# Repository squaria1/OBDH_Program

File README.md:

Description
-----------
Cranfield University, 2025 NB-IoT satellite constellation Group Design Project (GDP),<br />
On Board Data Handling (OBDH) program, Telemetry, Tracking, and Command (TT&C) basecamp cFS application and payload program, Electrical Power System (EPS) board KiCad project.

EPS board KiCad project
-----------------------
The EPS board is made from the fusion of two existing open source projects from https://libre.solar/:
* The MPPT: https://github.com/LibreSolar/mppt-2420-hc
* The BMS: https://github.com/LibreSolar/bms-8s50-ic

See https://learn.libre.solar/ for the documentation and schematic explanation.<br />

Notable changes from the two source projects are:
* Complete board rerouting
* Add fuse to MPPT input
* Changed DC-DC 12V circuit
* BMS output into MPPT battery input
* Separate BMS and MPPT ground planes
* CAN connectors from RJ-45 to DB9
* Only one DB9 connector for both MPPT and BMS
* Battery charging connector from Molex to JST-XH 8 pos (for a 7S LiPo battery)

OBDH and payload programs requirements
------------
* cmake (>v3.10)
* g++
* git
* linux environnement (or VM, WSL)

Optional
--------
* Doxygen (for documentation generation)

Common installation
-------------------
Install required packages,
```
sudo apt install cmake build-essential doxygen git
```

Clone from the github repository,
```
cd ~
git clone https://github.com/squaria1/OBDH_Program.git
```

OBDH program installation
-------------------------
Build the OBDH program,
```
cd ~/OBDH_Program
mkdir build
cd build
cmake -S ../ -B .
make
```

Run the OBDH program,
```
cd ~/OBDH_Program/build
sudo ./OBDH_Program
```

(Optional) Generate OBDH program documentation with Doxygen,
```
cd ../../doc
doxygen Doxyfile
```

Then open html/index.html with a web browser.

Payload program installation
----------------------------
Build the Payload program,
```
cd ~/OBDH_Program/Payload_Program
mkdir build
cd build
cmake -S ../ -B .
make
```

Run the Payload program,
```
cd ~/OBDH_Program/Payload_Program/build
sudo ./Payload_Program
```

(Optional) Generate Payload program documentation with Doxygen,
```
cd ../doc
doxygen Doxyfile
```

Then open html/index.html with a web browser.

cFS basecamp TT&C application installation
------------------------------------------
Follow cFS basecamp installation instructions on https://github.com/cfs-tools/cfs-basecamp,<br />

Run the basecamp GUI with (where env/ and cfs-basecamp/ directories are located),
```
source env/bin/activate
cd cfs-basecamp/gnd-sys/app/
. ./setvars.sh
python3 basecamp.py
```

Create the hi_world tutorial application with the basecamp GUI,<br />
File-->Create user app-->Toggle Hello World-->Create App

Add the hi_world app to the cFS build configuration,<br />
File-->Add User App to Target-->Select "hi_world" in the dropdown-->Click on "Auto"-->Close window

Replace,
```
"APP_CMD_PIPE_DEPTH": 5
```
In "cfs-basecamp/cfe-eds-framework/basecamp_defs/cpu1_hi_world_ini.json"<br />
By,
```
"APP_CMD_PIPE_MAX": 7
```

Close basecamp,<br />
File-->Exit

Remove generated basecamp hi_world/ and copy hi_world/ from the git to the basecamp installation,
```
rm -R <<CHANGE TO YOUR BASECAMP ENV DIRECTORY>>/cfs-basecamp/usr/apps/hi_world
cp -r ~/OBDH_Program/basecamp_cFS_custom_app/hi_world <<CHANGE TO YOUR BASECAMP ENV DIRECTORY>>/cfs-basecamp/usr/apps/
```

Start basecamp again,
```
python3 basecamp.py
```

Build the application,<br />
Click on "Build New"

Start the application,<br />
Click on "Start"

Send telecommands (TCs) to the OBDH Program or payload Program (send to the OBDH and rerouted to the payload program through the CAN bus),<br />
"Send Cmd" dropdown-->Select HI_WORLD/Application/CMD-->Select "SetParam" in the dropdown-->Select main state to change (only one at a time)

Show recieved telemetry (TM),<br />
"View Tlm" dropdown-->Select HI_WORLD/Application/STATUS_TLM

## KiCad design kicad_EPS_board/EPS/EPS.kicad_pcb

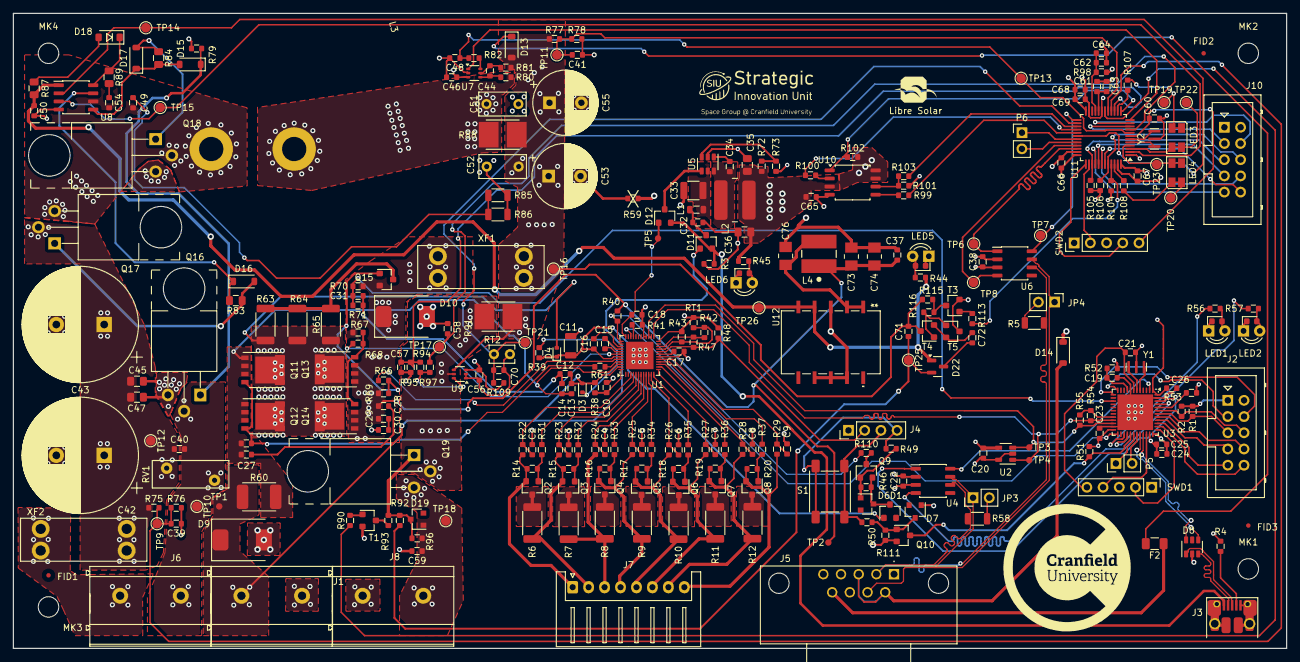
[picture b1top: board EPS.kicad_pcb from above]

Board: 4 copper layers, 199.5 x 99.5 mm, 305 parts (0 on the bottom side), 199 nets.

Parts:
C2, C3, C4, C5, C6, C7, C8, C9: 47n; C_0603_1608
C10: 470n; C_0603_1608
C11: 4.7u; C_1206_3216
C12, C14, C17, C32: 1u; C_0603_1608
C13: 10n; C_0603_1608
C15, C16, C31: 4.7n; C_0603_1608
C18, C19, C20, C21, C22, C23, C24, C26, C27, C28, C29, C30, C34: 100n; C_0603_1608
C25: 4.7u; C_0603_1608
C33: 4.7u; C_1210_3225
C35, C36: 10u; C_0805_2012
C37, C39, C40, C41, C57, C58, C59, C64, C72: 10nF; C_0603_1608
C38, C46, C54, C56, C60, C63, C65, C66, C67, C68, C70, C71: 100nF; C_0603_1608
C42, C43: 560µF; CP_Radial_D18.0mm_P7.50mm
C44, C48: 1nF; C_0603_1608
C45: 1µF; C_0805_2012
C47: 100nF; C_0805_2012
C49: 2.2nF; C_0603_1608
C50, C61, C62, C69: 2.2µF; C_0603_1608
C51, C52: 0.22µF; C_Rect_L7.2mm_W3.5mm_P5.00mm_FKS2_FKP2_MKS2_MKP2
C53, C55: 680µF; CP_Radial_D10.0mm_P5.00mm
C73, C74, C76: 4.7uF; CAPC370195_195N_KEM
D1, D11, D12: BAV70; SOT-23
D3, D4: PMEG6002; D_SOD-523
D6, D7, D19: 12V; D_SOT-23_ANK
D8: USBLC6-2SC6; SOT-23-6
D9, D10: SMCJ36A; D_SMC
D13, D14: NRVTS260ESFT1G; D_SOD-123
D15, D16, D17: SS14FL; D_SOD-123
D18: 1N4148; D_SOD-123
D22: BAS70-04; SOT-23
F2: 500mA; Fuse_1206_3216Metric
FID1, FID2, FID3: Fiducial; Fiducial_0.7mm
J1, J6, J8: MKDS 5/ 2-9,5; Phoenix_Contact_MKDS_5-2-9,5
J2, J10: UEXT; Box_Header_2x05x2.54mm_Straight
J3: USB_B_Micro; USB_Micro-B_10103594-0001LF
J4: Conn_01x04_Pin; PinHeader_1x04_P2.54mm_Vertical
J5: DE9_Receptacle; TE_2311765-1
J7: Conn_01x08_Pin; JST_XH_S8B-XH-A_1x08_P2.50mm_Horizontal
JP3, JP4: Jumper_NC_Small; PinHeader_1x02_P2.54mm_Vertical
L1: 4.7uH; L_0805_2012Metric
L2: 47uH; Bourns_SRN6045TA
L3: 53µH; Inductor_Toroid_D32.8mm_4mm2
L4: WE-PD2_5848
LED1, LED2, LED5, LED6: LED; LED_0603_D3.0mm
LED3, LED4: LED_Dual_PLCC4; LED_Avago_PLCC4_3.2x2.8mm_CW
LOGO1: LIBRE_SOLAR; LIBRESOLAR_LOGO
LOGO2: Cranfield University; cranfield_logo
LOGO3: Strategic Innovation Unit; strategic_innovation_unit
MK1, MK2, MK3, MK4: Mounting_Hole; MountingHole_3.2mm_M3
P5, P6: CONN_01X02; PinHeader_1x02_P2.54mm_Vertical
Q2, Q3, Q9: NDS0605; SOT-23
Q4, Q5, Q6, Q7, Q8, Q10, Q15: BSS138; SOT-23
Q11, Q12, Q13, Q14: BSC016N06NS; 5X6_MOSFET
Q16, Q17, Q18, Q19: IPA045N10N3G; TO-220-3_Horizontal_BottomHeatsink
R1, R2, R41, R54, R55, R76, R90, R97, R102, R105, R106: 2.2k; R_0603_1608
R3, R4, R14, R15, R16, R17, R18, R19, R20, R70: 330k; R_0603_1608
R5, R58: 120; R_1206_3216
R6, R7, R8, R9, R10, R11, R12: 33; R_2010_5025
R22, R23, R24, R25, R26, R27, R28, R29, R40, R44, R51, R56, R57, R82, R107, R108, R110, R116: 1k; R_0603_1608
R31, R32, R33, R34, R35, R36, R37, R43, R48, R49, R50, R93, R94, R109, R113: 10k; R_0603_1608
R38, R52, R61, R66, R68: 100; R_0603_1608
R39: 4R7; R_0603_1608
R42, R47, R71, R73: 22k; R_0603_1608
R45: 220; R_0603_1608
R46, R53, R62, R67, R69, R79, R96, R104, R111: 1M; R_0603_1608
R59: 0R; R_0603_1608
R60: 0.5m; R_Shunt_2512
R63, R64, R65: 330; R_2010_5025
R72: 50.5k; R_0603_1608
R75, R77, R92, R101, R115: 100k; R_0603_1608
R78: 5.6k; R_0603_1608
R80, R81: 10R; R_0603_1608
R83, R84, R87, R89: 3R3; R_0805_2012
R85, R86: 4R7; R_1206_3216
R88, R91: 2m; R_Bourns_CRE2512
R95: 8.2k; C_0603_1608
R98, R99, R100, R103: 47R; R_0603_1608
RT1: 10k; R_0603_1608
RT2: 10k; C_Disc_D3.8mm_W2.6mm_P2.50mm
RV1: 82V; RV_Disc_D12mm_W4.3mm_P7.5mm
S1: SW_PUSH; SW_SPST_6mm
SWD1: ST_Nucleo_SWD_5p; PinHeader_1x05_P2.54mm_Vertical
SWD2: ST_Nucleo_SWD; PinHeader_1x05_P2.54mm_Vertical
T1, T3, T4: BC846B; SOT-23
T5: BC856B; SOT-23
TP1: Bat+; TestPoint_1mm_pad
TP2: Ext+; TestPoint_1mm_pad
TP3: SDA; TestPoint_1mm_pad
TP4: SCL; TestPoint_1mm_pad
TP5: Regout; TestPoint_1mm_pad
TP6, TP7, TP8, TP9, TP10, TP11, TP12, TP13, TP14, TP15, TP16, TP17, TP18, TP19, TP20, TP21, TP22, TP23, TP25, TP26: 1.5mm; TestPoint_Pad_D1.5mm
U1: ISL94202; QFN-48-1EP_6x6mm_P0.4mm_EP4.3x4.3mm
U2: 24AA32; SOT-23-5
U3: STM32L452CCU6; QFN-48-1EP_7x7mm_P0.5mm_EP5.6x5.6mm
U4, U6: TCAN334; SOIC-8_3.9x4.9mm_Pitch1.27mm
U5: TPS560430X; SOT-23-6
U7, U9: INA186; SOT-363_SC-70-6
U8: LM5107; SOIC-8_3.9x4.9mm_Pitch1.27mm
U10: W25Q80DVS; SOIC-8_5.23x5.23mm_P1.27mm
U11: STM32G431CBTx; LQFP-48_7x7mm_P0.5mm
U12: TSR 0.5-24120SM; TSR 0.5SM_TRP
XF1, XF2: Fuse_Holder; Keystone-Fuse-3557-2
Y1, Y2: 8MHz; Resonator_Murata_CSTNE

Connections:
+3V3: C20.1, C22.1, C23.1, C24.1, C25.1, C26.1, C35.1, C36.1, C38.1, C46.1, C56.1, C65.1, C66.1, C67.1, C68.1, C69.1, J2.1 (3V3), J10.1 (3V3), L2.2, R1.2, R2.2, R45.2, R51.2, R52.2, R72.1, R98.2, R102.2, R105.2, R106.2, R109.1, SWD1.1 (VCC), SWD2.1 (VCC), U2.4 (VCC), U3.1 (VBAT), U3.24 (VDD), U3.36 (VDDUSB), U3.48 (VDD), U4.3 (VCC), U6.3 (VCC), U7.3 (V+), U9.3 (V+), U10.3 (IO2), U10.7 (IO3), U10.8 (VCC), U11.1 (VBAT), U11.24 (VDD), U11.36 (VDD), U11.48 (VDD)
+5V_BMS: D11.2 (A), D12.2 (A), J3.1 (VBUS), R3.1
+12V: C50.1, D22.1, R44.2, R87.2, TP26.1, U8.1 (VDD), U12.4 (+VOUT), U12.5 (+VOUT)
/8S BMS/BAT+: C12.1, C13.1, D3.2 (A), D9.1 (K), D11.1 (A), J1.1, R38.1, R60.2, TP1.1, U1.47 (CSI1)
/8S BMS/CAN_BMS_N: J5.2, R5.2, R58.2, U4.6 (CANL), U6.6 (CANL)
/8S BMS/CAN_BMS_P: J5.7, JP3.1, JP4.1, U4.7 (CANH), U6.7 (CANH)
/8S BMS/EXT+: C28.2, C29.1, C37.1, C73.1, C74.1, D10.1 (K), L4.1, Q13.S, Q14.S, Q15.2 (S), R40.1, R67.1, R69.1, R70.1, TP2.1, XF1.2
/8S BMS/ISL94202/ALERT: U1.34 (~SD), U3.25 (PB12)
/8S BMS/ISL94202/BTN_1: J4.4, R49.1, S1.2
/8S BMS/ISL94202/BTN_2: J4.3, R50.2, S1.1
/8S BMS/ISL94202/BTN_SIGNAL: Q10.3 (D), R51.1, U3.29 (PA8)
/8S BMS/ISL94202/CB1: R37.1, U1.16 (CB1)
/8S BMS/ISL94202/CB2: R36.1, U1.14 (CB2)
/8S BMS/ISL94202/CB3: R35.1, U1.12 (CB3)
/8S BMS/ISL94202/CB4: R34.1, U1.10 (CB4)
/8S BMS/ISL94202/CB5: R33.1, U1.8 (CB5)
/8S BMS/ISL94202/CB6: R32.1, U1.6 (CB6)
/8S BMS/ISL94202/CB7: R31.1, U1.4 (CB7)
/8S BMS/ISL94202/CELL1+: J7.7, Q7.2 (S), R12.2, R19.1, R28.2
/8S BMS/ISL94202/CELL1-: J7.8, Q8.2 (S), R20.1, R29.2
/8S BMS/ISL94202/CELL2+: J7.6, Q6.2 (S), R11.2, R18.1, R27.2
/8S BMS/ISL94202/CELL3+: J7.5, Q5.2 (S), R10.2, R17.1, R26.2
/8S BMS/ISL94202/CELL4+: J7.4, Q4.2 (S), R9.2, R16.1, R25.2
/8S BMS/ISL94202/CELL5+: J7.3, R7.1, R8.2, R24.2
/8S BMS/ISL94202/CELL6+: J7.2, Q3.2 (S), R6.1, R15.2, R23.2
/8S BMS/ISL94202/CELL7+: J7.1, Q2.2 (S), R14.2, R22.2
/8S BMS/ISL94202/CFET: R61.2, U1.45 (CFET)
/8S BMS/ISL94202/CHG+: D4.2 (A), Q11.D, Q12.D, Q13.D, Q14.D, R63.2, R64.2, R65.2
/8S BMS/ISL94202/CHMON: R40.2, R110.1, U1.37 (CHMON), U1.38 (LDMON)
/8S BMS/ISL94202/CSI2: C13.2, C14.1, C27.1, Q11.S, Q12.S, R60.1, R62.2, U1.46 (CSI2)
/8S BMS/ISL94202/DFET: R68.1, U1.42 (DFET)
/8S BMS/ISL94202/NTC_BAT: J4.2, R47.1, R48.2, U1.20 (XT1)
/8S BMS/ISL94202/PCFET: R66.2, U1.44 (PCFET)
/8S BMS/ISL94202/RGO: C18.1, D12.1 (A), TP5.1, U1.36 (RGO)
/8S BMS/ISL94202/SCL: R54.1, TP4.1, U1.25 (SCL), U2.1 (SCL), U3.21 (PB10)
/8S BMS/ISL94202/SDA: R55.1, TP3.1, U1.26 (SDAI), U1.27 (SDAO), U2.3 (SDA), U3.22 (PB11)
/8S BMS/ISL94202/TEMPO: R42.2, R47.2, U1.22 (TEMPO)
/8S BMS/ISL94202/VC0: C9.1, R29.1, U1.17 (VC0)
/8S BMS/ISL94202/VC1: C8.1, R28.1, U1.15 (VC1)
/8S BMS/ISL94202/VC2: C7.1, R27.1, U1.13 (VC2)
/8S BMS/ISL94202/VC3: C6.1, R26.1, U1.11 (VC3)
/8S BMS/ISL94202/VC4: C5.1, R25.1, U1.9 (VC4)
/8S BMS/ISL94202/VC5: C4.1, R24.1, U1.7 (VC5)
/8S BMS/ISL94202/VC6: C3.1, R23.1, U1.5 (VC6)
/8S BMS/ISL94202/VC7: C2.1, R22.1, U1.3 (VC7)
/8S BMS/ISL94202/VDD: C11.1, C16.1, D1.1 (A), D4.1 (K), R39.1, U1.43 (VDD)
/8S BMS/ISL94202/XT2: R42.1, R43.2, RT1.1, U1.21 (XT2)
/8S BMS/MCU/BOOT0: R53.2, U3.44 (PH3)
/8S BMS/MCU/CAN_RX: U3.45 (PB8), U4.4 (RXD)
/8S BMS/MCU/CAN_STB: U3.2 (PC13), U4.8 (STB)
/8S BMS/MCU/CAN_TX: U3.46 (PB9), U4.1 (TXD)
/8S BMS/MCU/I2C1_SCL: J2.5 (SCL), R1.1, U3.42 (PB6)
/8S BMS/MCU/I2C1_SDA: J2.6 (SDA), R2.1, U3.43 (PB7)
/8S BMS/MCU/I2C2_PULLUP: R54.2, R55.2, U3.20 (PB2)
/8S BMS/MCU/LED1: R56.2, U3.27 (PB14)
/8S BMS/MCU/LED2: R57.2, U3.28 (PB15)
/8S BMS/MCU/SPI1_MISO: J2.7 (MISO), U3.40 (PB4)
/8S BMS/MCU/SPI1_MOSI: J2.8 (MOSI), U3.41 (PB5)
/8S BMS/MCU/SPI1_SCK: J2.9 (SCK), U3.39 (PB3)
/8S BMS/MCU/SSEL: J2.10 (SSEL), U3.38 (PA15)
/8S BMS/MCU/SWCLK: SWD1.2 (SWCLK), U3.37 (PA14)
/8S BMS/MCU/SWDIO: SWD1.4 (SWDIO), U3.34 (PA13)
/8S BMS/MCU/USART1_RX: P5.2, U3.31 (PA10)
/8S BMS/MCU/USART1_TX: P5.1, U3.30 (PA9)
/8S BMS/MCU/USART2_RX: J2.4 (RXD), U3.13 (PA3)
/8S BMS/MCU/USART2_TX: J2.3 (TXD), U3.12 (PA2)
/8S BMS/MCU/USB_D+: D8.1 (IO1), J3.3 (D+)
/8S BMS/MCU/USB_D-: D8.3 (IO2), J3.2 (D-)
/8S BMS/MCU/USB_DN: D8.4 (IO2), U3.32 (PA11)
/8S BMS/MCU/USB_DP: D8.6 (IO1), U3.33 (PA12)
/8S BMS/MCU/~RESET: C21.1, SWD1.5 (NRST), U3.7 (NRST)
/8S BMS/Power Supply/EN: D12.3 (K), U5.4 (EN)
/8S BMS/Power Supply/FB: R72.2, R73.1, U5.3 (FB)
/8S BMS/Power Supply/SW: C34.2, L2.1, U5.6 (SW)
/8S BMS/Power Supply/VIN: C33.1, L1.2, U5.5 (Vin)
/8S BMS/V_EXT: C31.1, R70.2, R71.1, U3.15 (PA5)
/CAN_GND: D14.2 (A), J5.3, J5.6
/CAN_PWR: F2.1, J5.9
/MPPT/CAN/CAN_RX: TP8.1, U6.4 (RXD), U11.33 (PA11)
/MPPT/CAN/CAN_STB: TP7.1, U6.8 (STB), U11.25 (PB11)
/MPPT/CAN/CAN_TX: TP6.1, U6.1 (TXD), U11.34 (PA12)
/MPPT/DCDC/HS_DRV: D16.1 (K), R83.2, U8.7 (HO)
/MPPT/DCDC/I_DCDC: C48.1, R82.2, TP13.1, U11.8 (PA0)
/MPPT/DCDC/I_DCDC_REF: U7.1 (REF), U11.12 (PA4)
/MPPT/DCDC/LS_DRV: D15.2 (A), D17.1 (K), R84.2, U8.5 (LO)
/MPPT/DCDC/PWM_HS: TP14.1, U8.2 (HI), U11.30 (PA8)
/MPPT/DCDC/PWM_LS: TP15.1, U8.3 (LI), U11.2 (PC13)
/MPPT/DCDC/SHUNT_DCDC_P: C51.1, L3.2, R80.1, R88.2
/MPPT/DCDC/SW_NODE: C49.1, C54.2, L3.1, Q17.3 (S), Q18.2 (D), U8.6 (HS)
/MPPT/DCDC/V_DCDC_H: C39.1, R75.2, R76.1, TP9.1, U11.16 (PB0)
/MPPT/DCDC/V_DCDC_L: C41.1, R77.2, R78.1, TP11.1, U11.17 (PB1)
/MPPT/DCDC_HV+: C40.1, C42.1, C43.1, C45.1, C47.1, Q17.2 (D), R75.1, RV1.1, TP12.1, XF2.2
/MPPT/DCDC_HV-: C40.2, J6.2, Q16.2 (D), RV1.2, TP10.1
/MPPT/LOAD+: C59.1, D19.2 (A), J8.2, Q19.3 (S), R96.2, TP18.1
/MPPT/Load switch/CP_OUT: C71.1, D22.2, R92.1, TP25.1
/MPPT/Load switch/I_LOAD: C58.1, R97.2, TP17.1, U11.9 (PA1)
/MPPT/Load switch/I_LOAD_COMP: C57.1, R94.1, R95.2, U11.15 (PA7)
/MPPT/Load switch/LOAD_DIS: R90.1, U11.18 (PB2)
/MPPT/Load switch/SHUNT_LOAD_N: Q19.2 (D), R91.1, U9.5 (-)
/MPPT/MCU1/ADC1_IN11: C70.1, R109.2, RT2.1, TP21.1, U11.26 (PB12)
/MPPT/MCU1/GPIOC_14: LED3.2 (K1), LED3.3 (A2), TP22.1, U11.3 (PC14-OSC32_IN)
/MPPT/MCU1/GPIOC_15: LED4.2 (K1), LED4.3 (A2), TP23.1, U11.4 (PC15-OSC32_OUT)
/MPPT/MCU1/I2C1_SCL: J10.5 (SCL), R105.1, U11.39 (PA15)
/MPPT/MCU1/I2C1_SDA: J10.6 (SDA), R106.1, U11.44 (PB7)
/MPPT/MCU1/OSC_IN: U11.5 (PF0-OSC_IN), Y2.3
/MPPT/MCU1/OSC_OUT: U11.6 (PF1-OSC_OUT), Y2.1
/MPPT/MCU1/SPI1_MISO: J10.7 (MISO), U11.41 (PB4)
/MPPT/MCU1/SPI1_MOSI: J10.8 (MOSI), U11.42 (PB5)
/MPPT/MCU1/SPI1_SCK: J10.9 (SCK), U11.40 (PB3)
/MPPT/MCU1/SPI1_SSEL: J10.10 (SSEL), U11.43 (PB6)
/MPPT/MCU1/SPI2_CS: R102.1, U10.1 (~CS), U11.13 (PA5)
/MPPT/MCU1/SPI2_MISO: R100.1, U11.28 (PB14)
/MPPT/MCU1/SPI2_MOSI: R99.1, U11.29 (PB15)
/MPPT/MCU1/SPI2_SCK: R103.2, U11.27 (PB13)
/MPPT/MCU1/SWCLK: SWD2.2 (SWCLK), U11.38 (PA14)
/MPPT/MCU1/SWDIO: SWD2.4 (SWDIO), U11.37 (PA13)
/MPPT/MCU1/TIM8_CH2: R104.2, R113.2, U11.45 (PB8-BOOT0)
/MPPT/MCU1/TIM16_CH1: R107.2, U11.14 (PA6)
/MPPT/MCU1/TIM17_CH1: R108.2, U11.46 (PB9)
/MPPT/MCU1/USART1_RX: P6.2, U11.32 (PA10)
/MPPT/MCU1/USART1_TX: P6.1, U11.31 (PA9)
/MPPT/MCU1/USART2_RX: J10.4 (RXD), U11.11 (PA3)
/MPPT/MCU1/USART2_TX: J10.3 (TXD), U11.10 (PA2)
/MPPT/MCU1/~RESET: C60.1, SWD2.5 (NRST), U11.7 (NRST)
/MPPT/Power supply/CP_SW: C72.2, T4.2 (E), T5.2 (E)
/MPPT/Solar+: J6.1, XF2.1
GND: C30.2, C37.2, C38.2, C39.2, C41.2, C42.2, C43.2, C45.2, C46.2, C47.2, C48.2, C50.2, C51.2, C52.1, C53.2, C55.2, C56.2, C57.2, C58.2, C59.2, C60.2, C61.2, C62.2, C63.2, C64.2, C65.2, C66.2, C67.2, C68.2, C69.2, C70.2, C73.2, C74.2, C76.2, D9.2 (A), D10.2 (A), D14.1 (K), J1.2, J8.1, J10.2 (GND), LED5.1 (K), Q16.3 (S), Q18.3 (S), R59.1, R76.2, R78.2, R79.2, R85.1, R86.1, R95.1, R101.1, R104.1, RT2.2, SWD2.3 (GND), T1.2 (E), T3.2 (E), T5.3 (C), U6.2 (GND), U7.2 (GND), U8.4 (VSS), U9.1 (REF), U9.2 (GND), U10.4 (GND), U11.19 (VSSA), U11.23 (VSS), U11.35 (VSS), U11.47 (VSS), U12.3 (GGND), U12.7 (GND), U12.8 (GND), U12.9 (GND), Y2.2
GND_BMS: C2.2, C3.2, C4.2, C5.2, C6.2, C7.2, C8.2, C9.2, C10.2, C11.2, C12.2, C14.2, C17.2, C18.2, C19.2, C20.2, C21.2, C22.2, C23.2, C24.2, C25.2, C26.2, C31.2, C32.2, C33.2, C35.2, C36.2, D7.2 (A), D8.2 (GND), J2.2 (GND), J3.5 (GND), J3.6 (Shield), J4.1, LED1.1 (K), LED2.1 (K), LED6.1 (K), Q10.2 (S), R3.2, R4.2, R41.2, R43.1, R48.1, R53.1, R59.2, R71.2, R73.2, R111.1, RT1.2, SWD1.3 (GND), U1.18 (VSS), U1.24 (ADDR), U1.28 (VSS), U1.29 (VSS), U1.49 (PAD), U2.2 (GND), U2.5 (WP), U3.8 (VSSA), U3.23 (VSS), U3.35 (VSS), U3.47 (VSS), U3.49 (VSS), U4.2 (GND), U5.2 (GND), Y1.2
unnamed: C27.2, C28.1
unnamed: C29.2, C30.1
unnamed: C49.2, R85.2, R86.2
unnamed: C54.1, R89.2
unnamed: C72.1, D22.3
unnamed: C76.1, L4.2, U12.1 (+VIN), U12.2 (+VIN)
unnamed: D1.3 (K), D6.1 (K), Q9.2 (S), R46.2
unnamed: D3.1 (K), R39.2
unnamed: D6.2 (A), Q9.1 (G), R46.1, R49.2
unnamed: D7.1 (K), Q10.1 (G), R50.1, R111.2
unnamed: C32.1, D11.3 (K), L1.1
unnamed: D13.1 (K), F2.2
unnamed: D15.1 (K), Q16.1 (G), R79.1
unnamed: D16.2 (A), Q17.1 (G), R83.1
unnamed: D17.2 (A), Q18.1 (G), R84.1
unnamed: D18.2 (A), R87.1
unnamed: D18.1 (K), R89.1, U8.8 (HB)
unnamed: D19.1 (K), Q19.1 (G), R92.2, R93.2, R96.1
unnamed: J3.4 (ID), R4.1
unnamed: JP3.2, R58.1
unnamed: JP4.2, R5.1
unnamed: LED1.2 (A), R56.1
unnamed: LED2.2 (A), R57.1
unnamed: LED3.1 (A1), LED3.4 (K2), R107.1, TP19.1
unnamed: LED4.1 (A1), LED4.4 (K2), R108.1, TP20.1
unnamed: LED5.2 (A), R44.1
unnamed: LED6.2 (A), R45.1
unnamed: Q2.3 (D), R6.2
unnamed: Q2.1 (G), R14.1, R31.2
unnamed: Q3.3 (D), R7.2
unnamed: Q3.1 (G), R15.1, R32.2
unnamed: Q4.3 (D), R8.1
unnamed: Q4.1 (G), R16.2, R33.2
unnamed: Q5.3 (D), R9.1
unnamed: Q5.1 (G), R17.2, R34.2
unnamed: Q6.3 (D), R10.1
unnamed: Q6.1 (G), R18.2, R35.2
unnamed: Q7.3 (D), R11.1
unnamed: Q7.1 (G), R19.2, R36.2
unnamed: Q8.3 (D), R12.1
unnamed: Q8.1 (G), R20.2, R37.2
unnamed: Q9.3 (D), R110.2
unnamed: Q11.G, Q12.G, R61.1, R62.1
unnamed: Q13.G, Q14.G, R67.2, R68.2
unnamed: Q15.3 (D), R63.1, R64.1, R65.1
unnamed: Q15.1 (G), R66.1, R69.2
unnamed: R82.1, U7.6
unnamed: R94.2, R97.1, U9.6
unnamed: R90.2, T1.1 (B)
unnamed: R93.1, T1.3 (C)
unnamed: R113.1, T3.1 (B)
unnamed: R115.1, R116.1, T3.3 (C)
unnamed: R116.2, T4.1 (B), T5.1 (B)
unnamed: C15.1, U1.41 (C1)
unnamed: C15.2, U1.40 (C2)
unnamed: C16.2, U1.39 (C3)
unnamed: R41.1, U1.33 (FETSOFF)
unnamed: C10.1, R38.2, U1.48 (VBATT)
unnamed: C17.1, U1.19 (VREF)
unnamed: U3.5 (PH0), Y1.3
unnamed: U3.6 (PH1), Y1.1
unnamed: C19.1, R52.1, U3.9 (VDDA)
unnamed: C34.1, U5.1 (CB)
unnamed: C44.1, R80.2, U7.4 (+)
unnamed: C44.2, R81.2, U7.5 (-)
unnamed: R101.2, R103.1, U10.6 (CLK)
unnamed: R99.2, U10.5 (DI(IO0))
unnamed: R100.2, U10.2 (DO(IO1))
VBUS: C52.2, C53.1, C55.1, C71.2, D13.2 (A), R77.1, R81.1, R88.1, R91.2, R115.2, T4.3 (C), TP16.1, U9.4 (+), XF1.1
VDDA: C62.1, C64.1, R98.1, U11.21 (VDDA)
VREF: C61.1, C63.1, U11.20 (VREF+)

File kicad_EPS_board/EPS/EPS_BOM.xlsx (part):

Id | Reference | Value | Footprint | Qty | Name | Price in £ | url
1 | J7 |  | JST_XH_S8B-XH-A_1x08_P2.50mm_Horizontal | 1 | S8B-XH-A-1 | 0.33 | https://www.digikey.co.uk/en/products/detail/jst-sales-ameri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
2 | XF2,XF1 |  | Keystone-Fuse-3557-2 | 2 | 3557-2 | 2.02 | https://www.digikey.co.uk/en/products/detail/keystone-electr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
3 | J4 |  | PinHeader_1x03_P2.54mm_Vertical | 1 | 61303211121 | 1.62 | https://www.digikey.co.uk/en/products/detail/w%C3%BCrth-elek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
4 | S1 |  | SW_SPST_6mm | 1 | TL3301NF160QG-KR | 0.19 | https://www.digikey.co.uk/en/products/detail/e-switch/TL3301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
5 | R111,R46,R53,R104,R79,R62,R96,R67,R69 | 1M | R_0603_1608 | 9 | ERJ-3EKF1004V | 0.28000000000000003 | https://www.digikey.co.uk/en/products/detail/panasonic-elect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
6 | R110,R57,R44,R40,R22,R25,R107,R108,R82,R28,R51,R27,R26,R23,R56,R29,R116,R24 | 1k | R_0603_1608 | 18 | RC0603FR-071KL | 0.14000000000000001 | https://www.digikey.co.uk/en/products/detail/yageo/RC0603FR-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
7 | R50,R49,R109,R43,R113,R37,R94,R34,R93,R31,RT1,R33,R35,R36,R32,R48 | 10k | R_0603_1608 | 16 | ERJ-3GEYJ103V | 0.43 | https://www.digikey.co.uk/en/products/detail/panasonic-elect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
8 | Q10,Q15,Q5,Q4,Q6,Q8,Q7 |  | SOT-23 | 7 | BSS138 | 1.28 | https://www.digikey.co.uk/en/products/detail/onsemi/BSS138/244210
9 | Q9,Q2,Q3 |  | SOT-23 | 3 | NDS0605 | 0.6 | https://www.digikey.co.uk/en/products/detail/onsemi/NDS0605/244214
10 | D7,D6,D19 |  | D_SOT-23_ANK | 3 | SZBZX84C12LT3G | 0.39 | https://www.digikey.co.uk/en/products/detail/onsemi/SZBZX84C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
11 | J5 |  | TE_2311765-1 | 1 | 2311765-1 | 1.75 | https://www.digikey.co.uk/en/products/detail/te-connectivity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
12 | U12 |  | TSR 0.5SM_TRP | 1 | TSR 0.5-24120SM | 6.51 | https://www.digikey.co.uk/en/products/detail/traco-power/TSR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
13 | R5,R58 | 120R | R_1206_3216 | 2 | RC1206FR-07120RL | 0.08 | https://www.digikey.co.uk/en/products/detail/yageo/rc1206fr-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
14 | R20,R14,R3,R4,R16,R18,R19,R17,R15,R70 | 330k | R_0603_1608 | 10 | RC0603FR-07330KL | 0.08 | https://www.digikey.co.uk/en/products/detail/yageo/RC0603FR-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
15 | C40,C41,C57,C58,C37,C39,C64,C72,C59,C13 | 10nF | C_0603_1608 | 9 | C1608X7R2A103M080AA | 0.31 | https://www.digikey.co.uk/en/products/detail/tdk-corporation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
16 | D14,D2,D13,D1 |  | D_SOD-123 | 4 | MB2H60AL-AU_R1_000A1 | 1.1599999999999999 | https://www.digikey.co.uk/en/products/detail/panjit-internat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
17 | R6,R12,R8,R10,R7,R11,R9 | 33R | R_2010_5025 | 7 | RC2010JK-0733RL | 0.41 | https://www.digikey.co.uk/en/products/detail/yageo/RC2010JK-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
18 | R84,R89,R87,R83 | 3R3 | R_0805_2012 | 4 | RC0805FR-073R3L | 0.16 | https://www.digikey.co.uk/en/products/detail/yageo/RC0805FR-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
19 | LED5,LED6,LED1,LED2 |  | LED_0603_D3.0mm | 4 | LTST-C190KFKT | 0.64 | https://www.digikey.co.uk/en/products/detail/liteon/LTST-C19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
20 | L4 | 10uH | WE-PD2_5848 | 1 | 74477410 | 1.69 | https://www.digikey.co.uk/en/products/detail/w%C3%BCrth-elek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
21 | C38,C71,C65,C66,C63,C56,C67,C68,C54,C46,C70,C60,C24,C20,C26,C22,C30,C28,C29,C27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 | 100nF | C_0603_1608 | 25 | CC0603ZRY5V9BB104 | 0.18 | https://www.digikey.co.uk/en/products/detail/yageo/CC0603ZRY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
22 | U6,U4 |  | SOIC-8_3.9x4.9mm_Pitch1.27mm | 2 | TCAN334D | 4.58 | https://www.digikey.co.uk/en/products/detail/texas-instrumen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
23 | Y2,Y1 | 8MHz | Resonator_Murata_CSTNE | 2 | CSTNE8M00GH5C000R0 | 0.46 | https://www.digikey.co.uk/en/products/detail/murata-electron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
24 | C47 | 100nF | C_0805_2012 | 1 | CLLE1AX7S0G104M050AC | 0.19 | https://www.digikey.co.uk/en/products/detail/tdk-corporation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
25 | R103,R100,R98,R99 | 47R | R_0603_1608 | 4 | RC0603FR-0747RL | 0.32 | https://www.digikey.co.uk/en/products/detail/yageo/RC0603FR-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
26 | R39 | 4R7 | R_0603_1608 | 1 | RC0603FR-071KL | 0.1 | https://www.digikey.co.uk/en/products/detail/yageo/RC0603FR-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
27 | R90,R76,R97,R1,R106,R105,R102,R2,R41,R54,R55 | 2.2k | R_0603_1608 | 11 | CRGCQ0603F2K2 | 0.25 | https://www.digikey.co.uk/en/products/detail/te-connectivity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
28 | R86,R85 | 4R7 | R_1206_3216 | 2 | RC1206FR-074R7L | 0.22 | https://www.digikey.co.uk/en/products/detail/yageo/RC1206FR-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
29 | T1,T4,T3 |  | SOT-23 | 3 | BC846B | 0.24 | https://www.digikey.co.uk/en/products/detail/diotec-semicond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
30 | LED4,LED3 |  | LED_Avago_PLCC4_3.2x2.8mm_CW | 2 | LTST-E682KRKGWT | 0.54 | https://www.digikey.co.uk/en/products/detail/liteon/LTST-E68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
31 | C16,C15,C31 | 4.7nF | C_0603_1608 | 3 | CC0603KRX7R9BB472 | 0.18 | https://www.digikey.co.uk/en/products/detail/yageo/CC0603KRX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
32 | C5,C8,C4,C6,C9,C2,C3,C7 | 47nF | C_0603_1608 | 8 | CC0603KRX7R9BB473 | 0.26 | https://www.digikey.co.uk/en/products/detail/yageo/CC0603KRX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
33 | J10,J2 |  | Box_Header_2x05x2.54mm_Straight | 2 | 61201021621 | 0.7 | https://www.digikey.co.uk/en/products/detail/w%C3%BCrth-elek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
34 | Q11,Q12,Q13,Q14 |  | 5X6_MOSFET | 4 | BSC016N06NSATMA1 | 9.44 | https://www.digikey.co.uk/en/products/detail/infineon-techno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
35 | U1 |  | QFN-48-1EP_6x6mm_P0.4mm_EP4.3x4.3mm | 1 | ISL94202IRTZ-T7A | 9.82 | https://www.digikey.co.uk/en/products/detail/renesas-electro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
36 | R101,R92,R77,R75,R115 | 100k | R_0603_1608 | 5 | RC0603FR-07100KL | 7.0000000000000007E-2 | https://www.digikey.co.uk/en/products/detail/yageo/RC0603FR-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
37 | T5 |  | SOT-23 | 1 | BC856B | 0.08 | https://www.digikey.co.uk/en/products/detail/diotec-semicond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
38 | R38,R66,R52,R61,R68 | 100R | R_0603_1608 | 5 | RC0603FR-07100RL | 0.08 | https://www.digikey.co.uk/en/products/detail/yageo/RC0603FR-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
39 | C48,C44 | 1nF | C_0603_1608 | 2 | C0603C102K5RACTU | 0.12 | https://www.digikey.co.uk/en/products/detail/kemet/C0603C102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
40 | L3 |  | Inductor_Toroid_D32.8mm_4mm2 | 1 | 53µH | 8.4499999999999993 | https://uk.rs-online.com/web/p/copper-wire/7790703?gb=s
41 | U11 |  | LQFP-48_7x7mm_P0.5mm | 1 | STM32G431CBTx | 4.28 | https://www.digikey.co.uk/en/products/detail/stmicroelectron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
42 | R65,R63,R64 | 330R | R_2010_5025 | 3 | RC2010JK-07330RL | 0.33 | https://www.digikey.co.uk/en/products/detail/yageo/RC2010JK-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
43 | R95 | 8.2k | C_0603_1608 | 1 | RC0603FR-078K2L | 0.08 | https://www.digikey.co.uk/en/products/detail/yageo/RC0603FR-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
44 | U9,U7 |  | SOT-363_SC-70-6 | 2 | INA186A1IDCKR | 1.82 | https://www.digikey.co.uk/en/products/detail/texas-instrumen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
45 | D16,D17,D15 |  | D_SOD-123 | 3 | MBR140SFT1G | 0.99 | https://www.digikey.co.uk/en/products/detail/onsemi/MBR140SF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
46 | R42,R73,R47,R71 | 22k | R_0603_1608 | 4 | RC0603FR-0722KL | 0.09 | https://www.digikey.co.uk/en/products/detail/yageo/RC0603FR-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
47 | R60 | 0.5m | R_Shunt_2512 | 1 | WSLF2512L5000FEA | 0.84 | https://www.digikey.co.uk/en/products/detail/vishay-dale/WSL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
48 | C76,C74,C73 | 4.7uF | CAPC370195_195N_KEM | 3 | C1206X475J5RACAUTO | 1.92 | https://www.digikey.co.uk/en/products/detail/kemet/C1206X475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
49 | C49,C61,C62,C69,C50 | 2.2nF | C_0603_1608 | 5 | C0603C222J1GACTU | 1.25 | https://www.digikey.co.uk/en/products/detail/kemet/C0603C222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
50 | D3,D4 |  | D_SOD-523 | 2 | PMEG6002 | 0.56000000000000005 | https://www.digikey.co.uk/en/products/detail/nexperia-usa-in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
51 | C33 | 4.7uF | C_1210_3225 | 2 | GRM31CR71H475MA12L | 0.56999999999999995 | https://www.digikey.co.uk/en/products/detail/murata-electron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
52 | C10 | 470nF | C_0603_1608 | 1 | GRM188R71E474KA12D | 0.09 | https://www.digikey.co.uk/en/products/detail/murata-electron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
53 | R81,R80 | 10R | R_0603_1608 | 2 | RC0603FR-0710RL | 0.08 | https://www.digikey.co.uk/en/products/detail/yageo/RC0603FR-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
54 | C36,C35 | 10uF | C_0805_2012 | 2 | GRM21BR61E106KA73L | 0.31 | https://www.digikey.co.uk/en/products/detail/murata-electron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
55 | D11,D12 |  | SOT-23 | 3 | BAV70LT1G | 0.24 | https://www.digikey.co.uk/en/products/detail/onsemi/BAV70LT1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
56 | D18 |  | D_SOD-123 | 1 | 1N4148 | 0.08 | https://www.digikey.co.uk/en/products/detail/diodes-incorpor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
57 | J1,J8,J6 |  | Phoenix_Contact_MKDS_5-2-9,5 | 3 | 1714971 | 4.9800000000000004 | https://www.digikey.co.uk/en/products/detail/phoenix-contact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
58 | L2 | 47uH | Bourns_SRN6045TA | 1 | SRN6045TA-470M | 0.36 | https://www.digikey.co.uk/en/products/detail/bourns-inc/srn6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

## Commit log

2025-02-16 Create test
2025-02-17 test
2025-02-18 Add CCSDS Library
2025-02-19 cFS UDP TC and Telem connection
2025-02-21 TC and Telem TT&C basecamp cFS
2025-02-24 Add sensor parameters file and checks
2025-02-24 Improve comments
2025-02-25 Payload subsystem added
2025-02-27 Payload management functions added
2025-02-27 state machines completed
2025-02-28 correct memory leak
2025-03-03 EPS board KiCad project added and Doxygen integration
2025-03-05 fix can 1
2025-03-07 CAN update
2025-03-07 can0
2025-03-09 sensor val history files added
2025-04-23 kicad EPS board V2 revision and already generated html doc files
